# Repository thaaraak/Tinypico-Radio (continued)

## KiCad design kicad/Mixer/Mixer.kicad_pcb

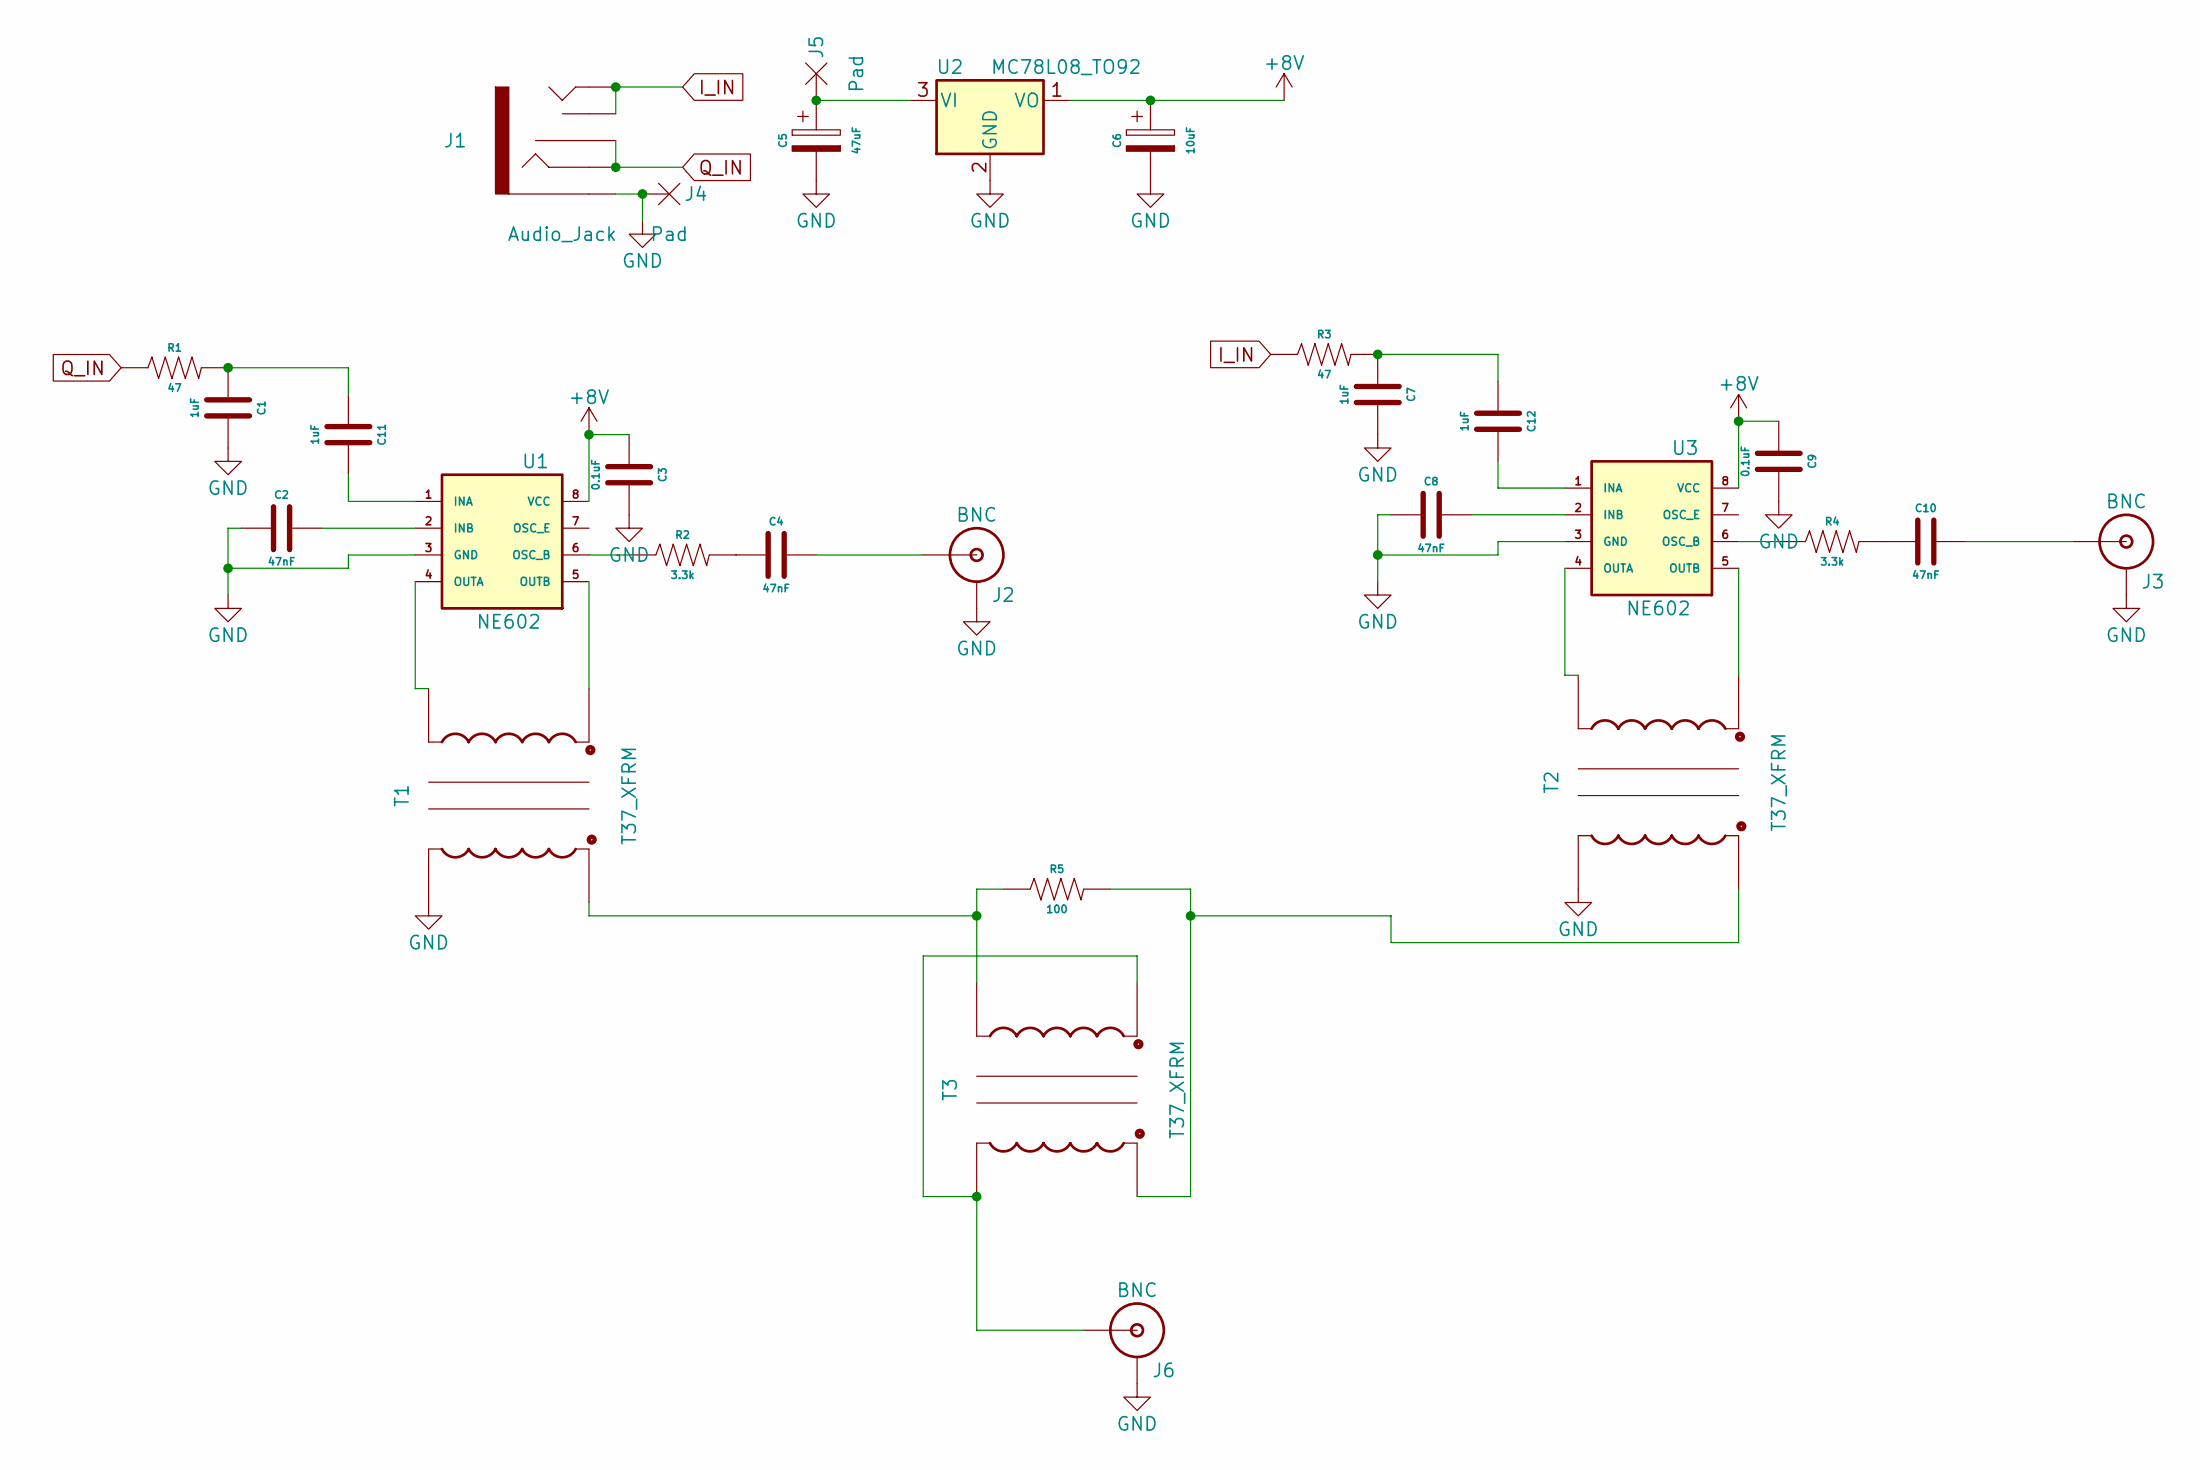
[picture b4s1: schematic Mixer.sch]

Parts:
C1, C7, C11, C12: 1uF; CAP-PTH-5MM
C2, C4, C8, C10: 47nF; CAP-PTH-5MM
C3, C9: 0.1uF; CAP-PTH-5MM
C5: 47uF; CPOL-RADIAL-2.5MM-6.5MM
C6: 10uF; CPOL-RADIAL-2.5MM-6.5MM
J1: Audio_Jack
J2, J3, J6: BNC
J4, J5: Pad
R1, R3: 47; R_Axial_DIN0204_L3.6mm_D1.6mm_P2.54mm_Vertical
R2, R4: 3.3k; R_Axial_DIN0204_L3.6mm_D1.6mm_P2.54mm_Vertical
R5: 100; R_Axial_DIN0204_L3.6mm_D1.6mm_P2.54mm_Vertical
T1, T2, T3: T37_XFRM; T37 Transformer
U1, U3: NE602; DIP8
U2: MC78L08_TO92; TO-92_Inline

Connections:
+8V: C3.1, C6.1, C9.1, U1.8 (VCC), U2.1 (VO), U3.8 (VCC)
GND: C1.2, C2.1, C3.2, C5.2, C6.2, C7.2, C8.1, C9.2, J1.SLEEVE, J2.GND, J3.GND, J4.1, J6.GND, T1.C2A, T2.C2A, U1.3 (GND), U2.2 (GND), U3.3 (GND)
I_IN: J1.TIP, J1.TSH, R3.1
unnamed: C1.1, C11.1, R1.2
unnamed: C2.2, U1.2 (INB)
unnamed: C4.1, R2.2
unnamed: C4.2, J2.S (OUT)
unnamed: C5.1, J5.1, U2.3 (VI)
unnamed: C8.2, U3.2 (INB)
unnamed: C10.1, R4.2
unnamed: C10.2, J3.S (OUT)
unnamed: C11.2, U1.1 (INA)
unnamed: C7.1, C12.1, R3.2
unnamed: C12.2, U3.1 (INA)
unnamed: J6.S (OUT), T3.C1B, T3.C2A
unnamed: R2.1, U1.6 (OSC_B)
unnamed: R4.1, U3.6 (OSC_B)
unnamed: R5.1, T1.C2B, T3.C1A
unnamed: R5.2, T2.C2B, T3.C2B
unnamed: T1.C1A, U1.4 (OUTA)
unnamed: T1.C1B, U1.5 (OUTB)
unnamed: T2.C1A, U3.4 (OUTA)
unnamed: T2.C1B, U3.5 (OUTB)
Q_IN: J1.RING, J1.RSH, R1.1

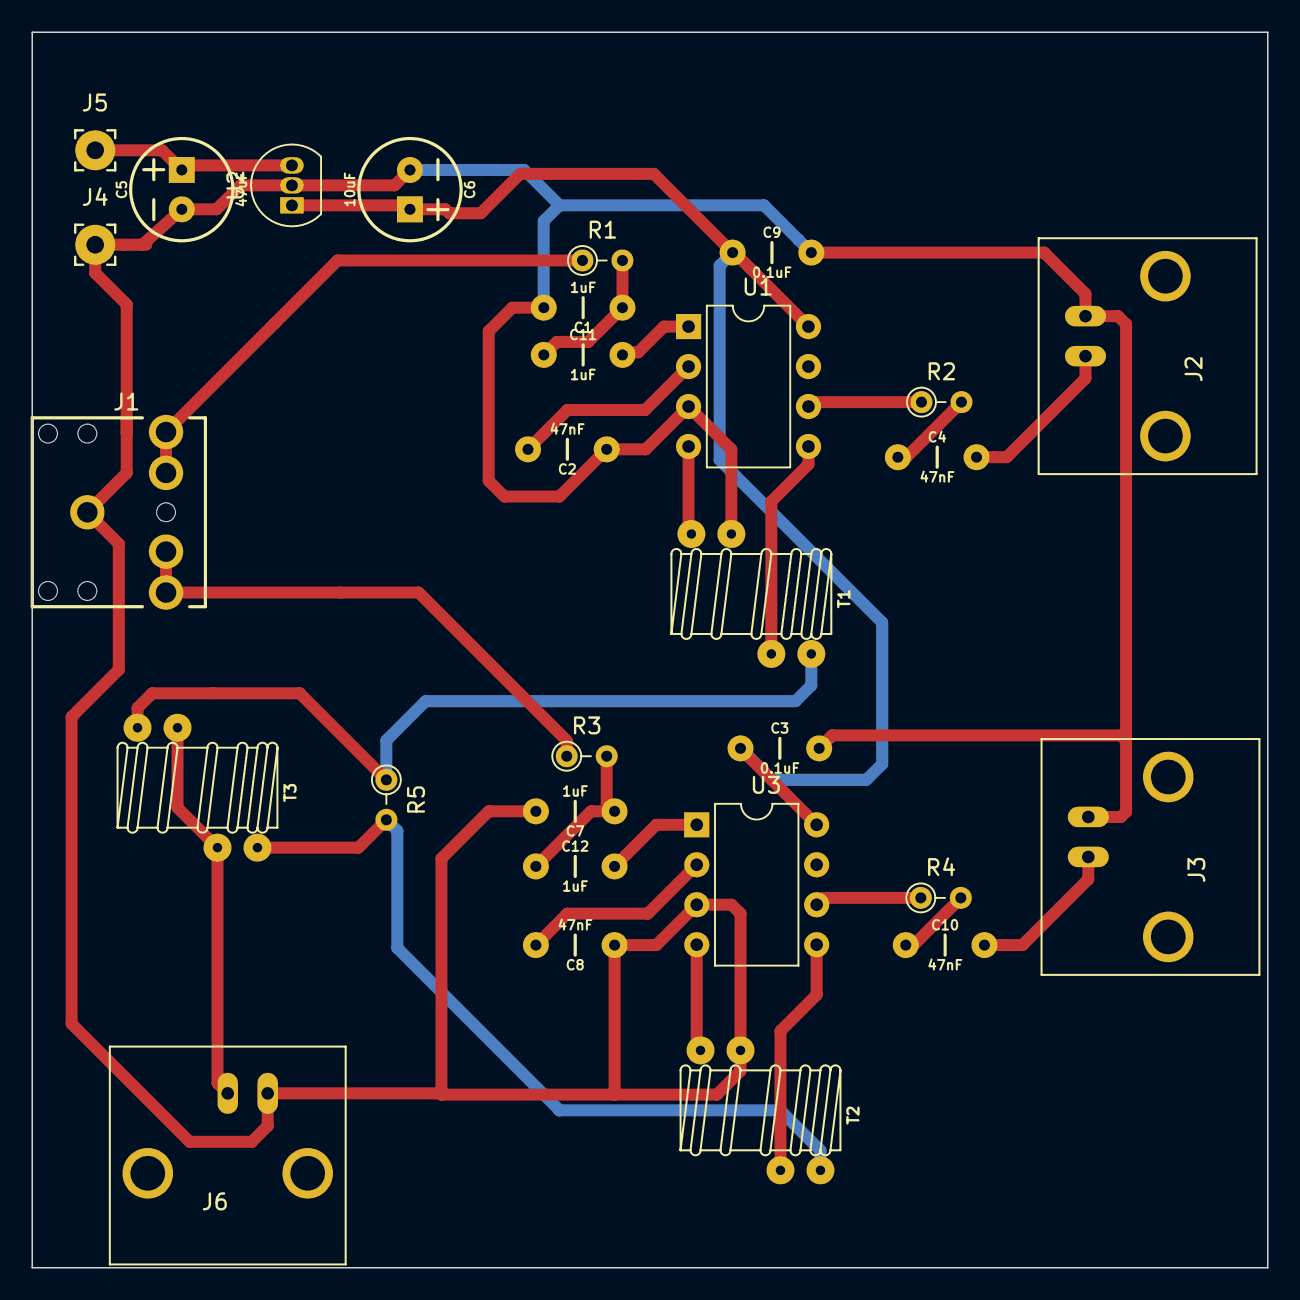
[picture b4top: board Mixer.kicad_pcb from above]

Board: 2 copper layers, 78.5 x 78.5 mm, 29 parts (0 on the bottom side), 24 nets.

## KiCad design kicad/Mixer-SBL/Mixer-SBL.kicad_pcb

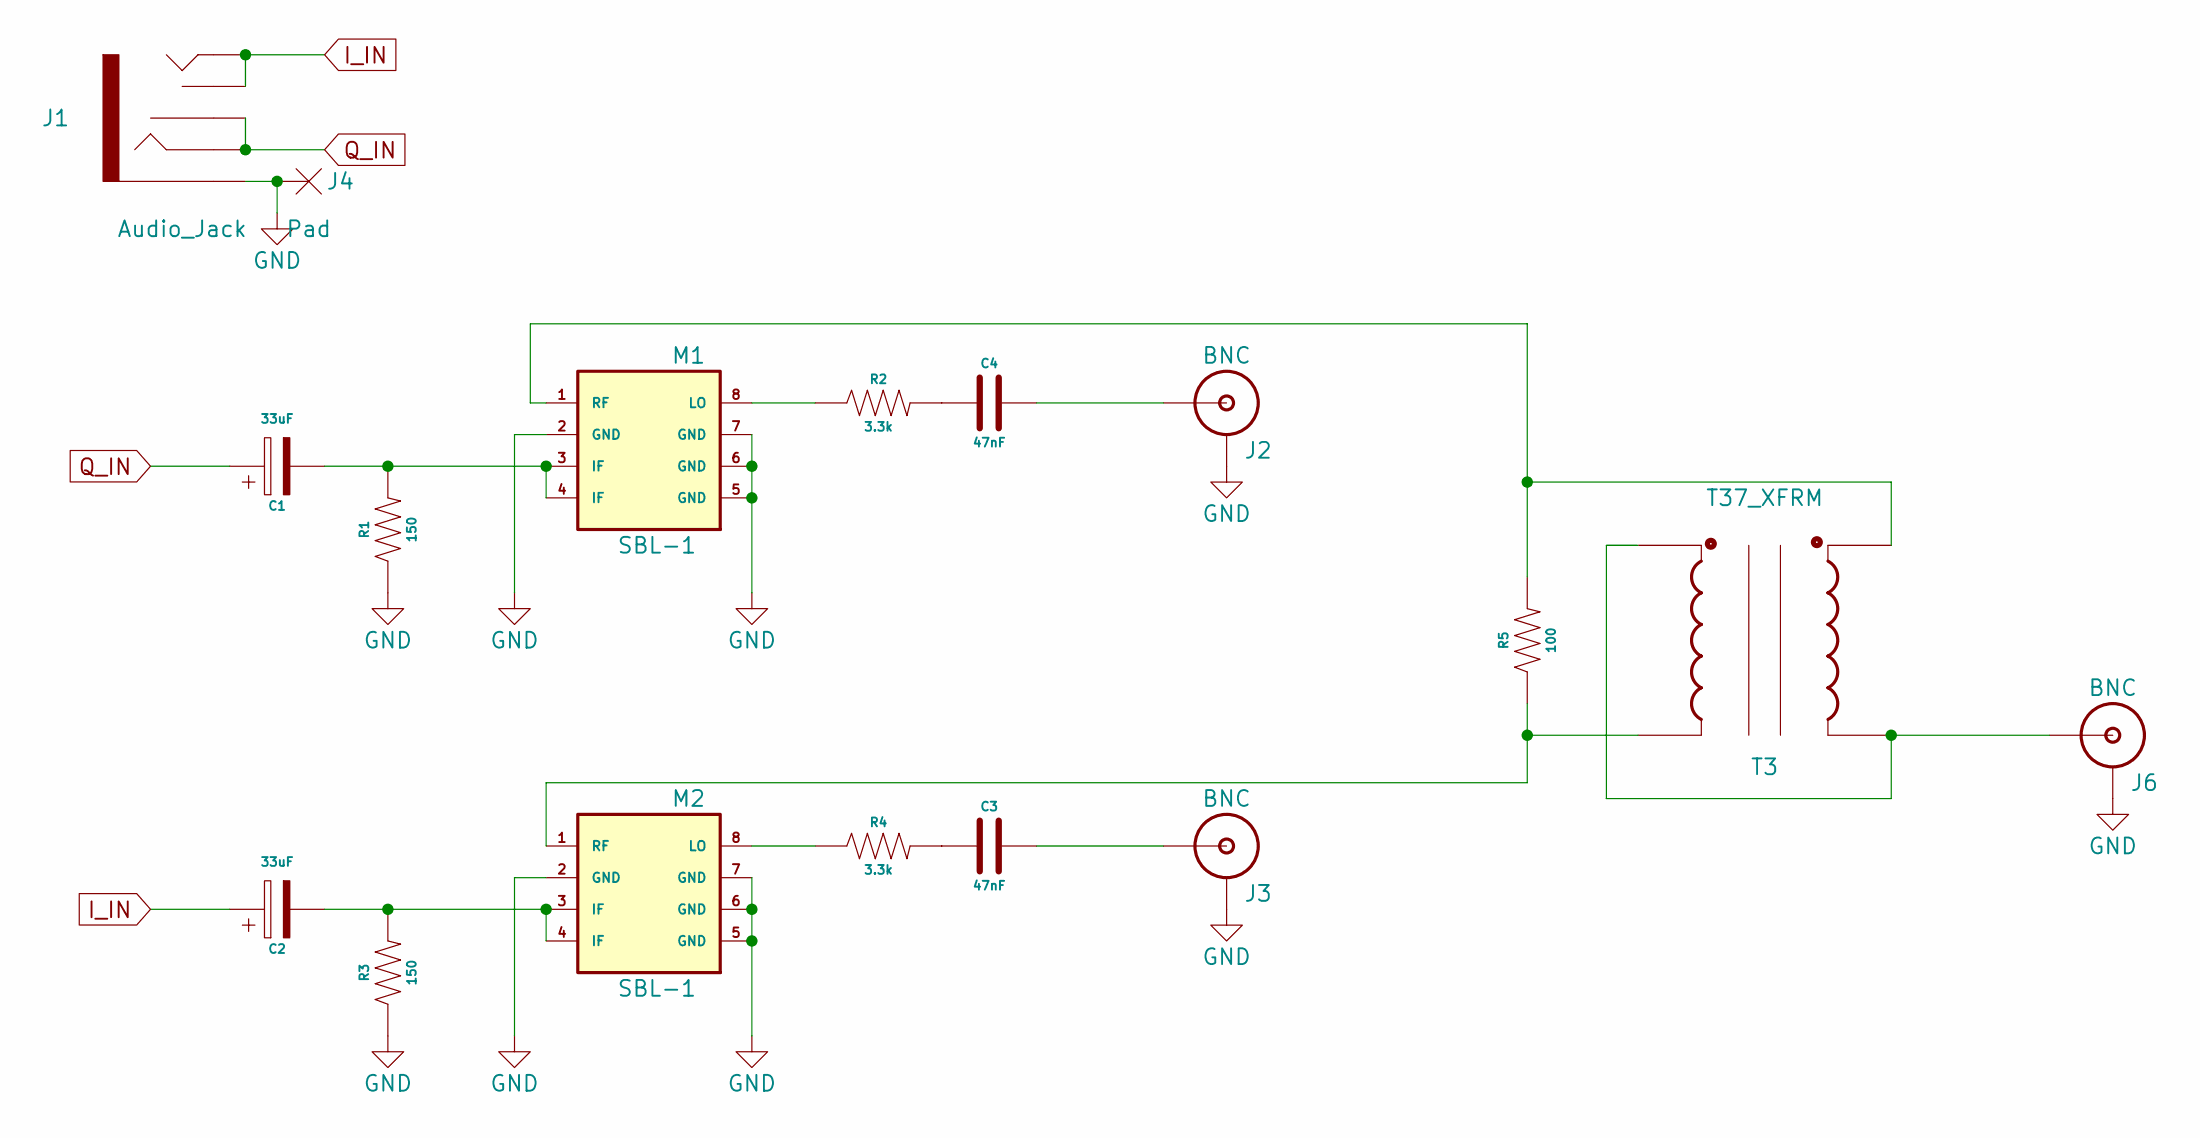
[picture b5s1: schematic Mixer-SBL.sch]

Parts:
C1, C2: 33uF; CPOL-RADIAL-2.5MM-5MM
C3, C4: 47nF; CAP-PTH-5MM
J1: Audio_Jack
J2, J3, J6: BNC
J4: Pad
M1, M2: SBL-1
R1, R3: 150; R_Axial_DIN0204_L3.6mm_D1.6mm_P2.54mm_Vertical
R2, R4: 3.3k; R_Axial_DIN0204_L3.6mm_D1.6mm_P2.54mm_Vertical
R5: 100; R_Axial_DIN0204_L3.6mm_D1.6mm_P2.54mm_Vertical
T3: T37_XFRM; T37 Transformer

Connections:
GND: J1.SLEEVE, J2.GND, J3.GND, J4.1, J6.GND, M1.2 (GND), M1.5 (GND), M1.6 (GND), M1.7 (GND), M2.2 (GND), M2.5 (GND), M2.6 (GND), M2.7 (GND), R1.1, R3.1
I_IN: C2.1, J1.TIP, J1.TSH
unnamed: C1.2, M1.3 (IF), M1.4 (IF), R1.2
unnamed: C2.2, M2.3 (IF), M2.4 (IF), R3.2
unnamed: C3.1, R4.2
unnamed: C3.2, J3.S (OUT)
unnamed: C4.1, R2.2
unnamed: C4.2, J2.S (OUT)
unnamed: J6.S (OUT), T3.C1B, T3.C2A
unnamed: M1.1 (RF), R5.2, T3.C2B
unnamed: M1.8 (LO), R2.1
unnamed: M2.1 (RF), R5.1, T3.C1A
unnamed: M2.8 (LO), R4.1
Q_IN: C1.1, J1.RING, J1.RSH

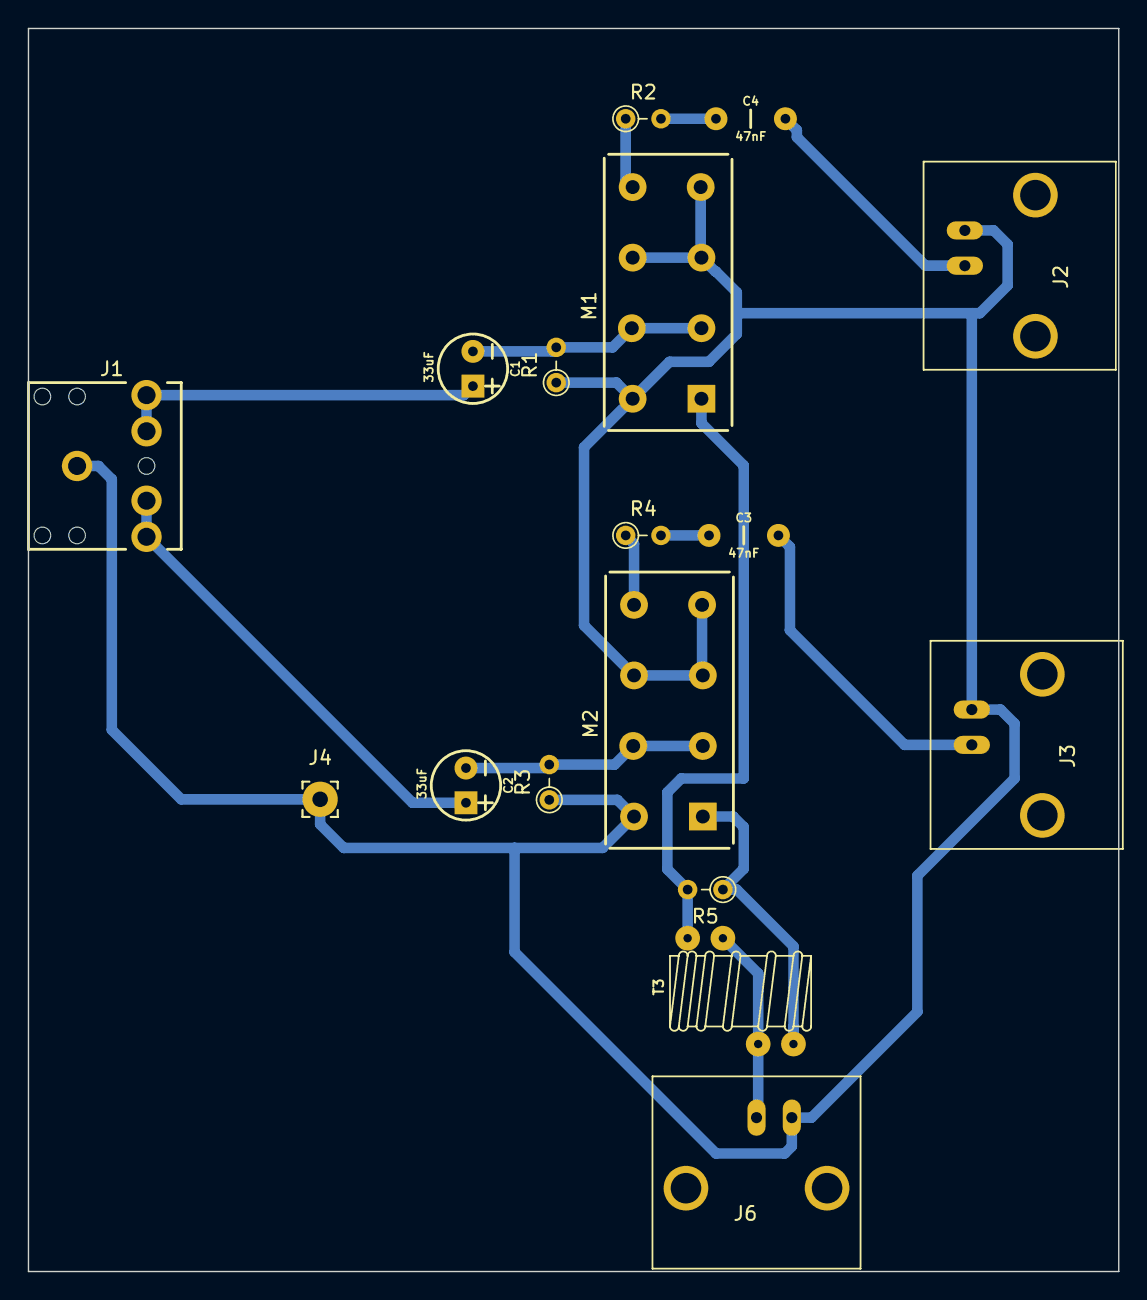
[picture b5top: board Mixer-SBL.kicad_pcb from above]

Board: 2 copper layers, 78.5 x 89.5 mm, 17 parts (0 on the bottom side), 14 nets.

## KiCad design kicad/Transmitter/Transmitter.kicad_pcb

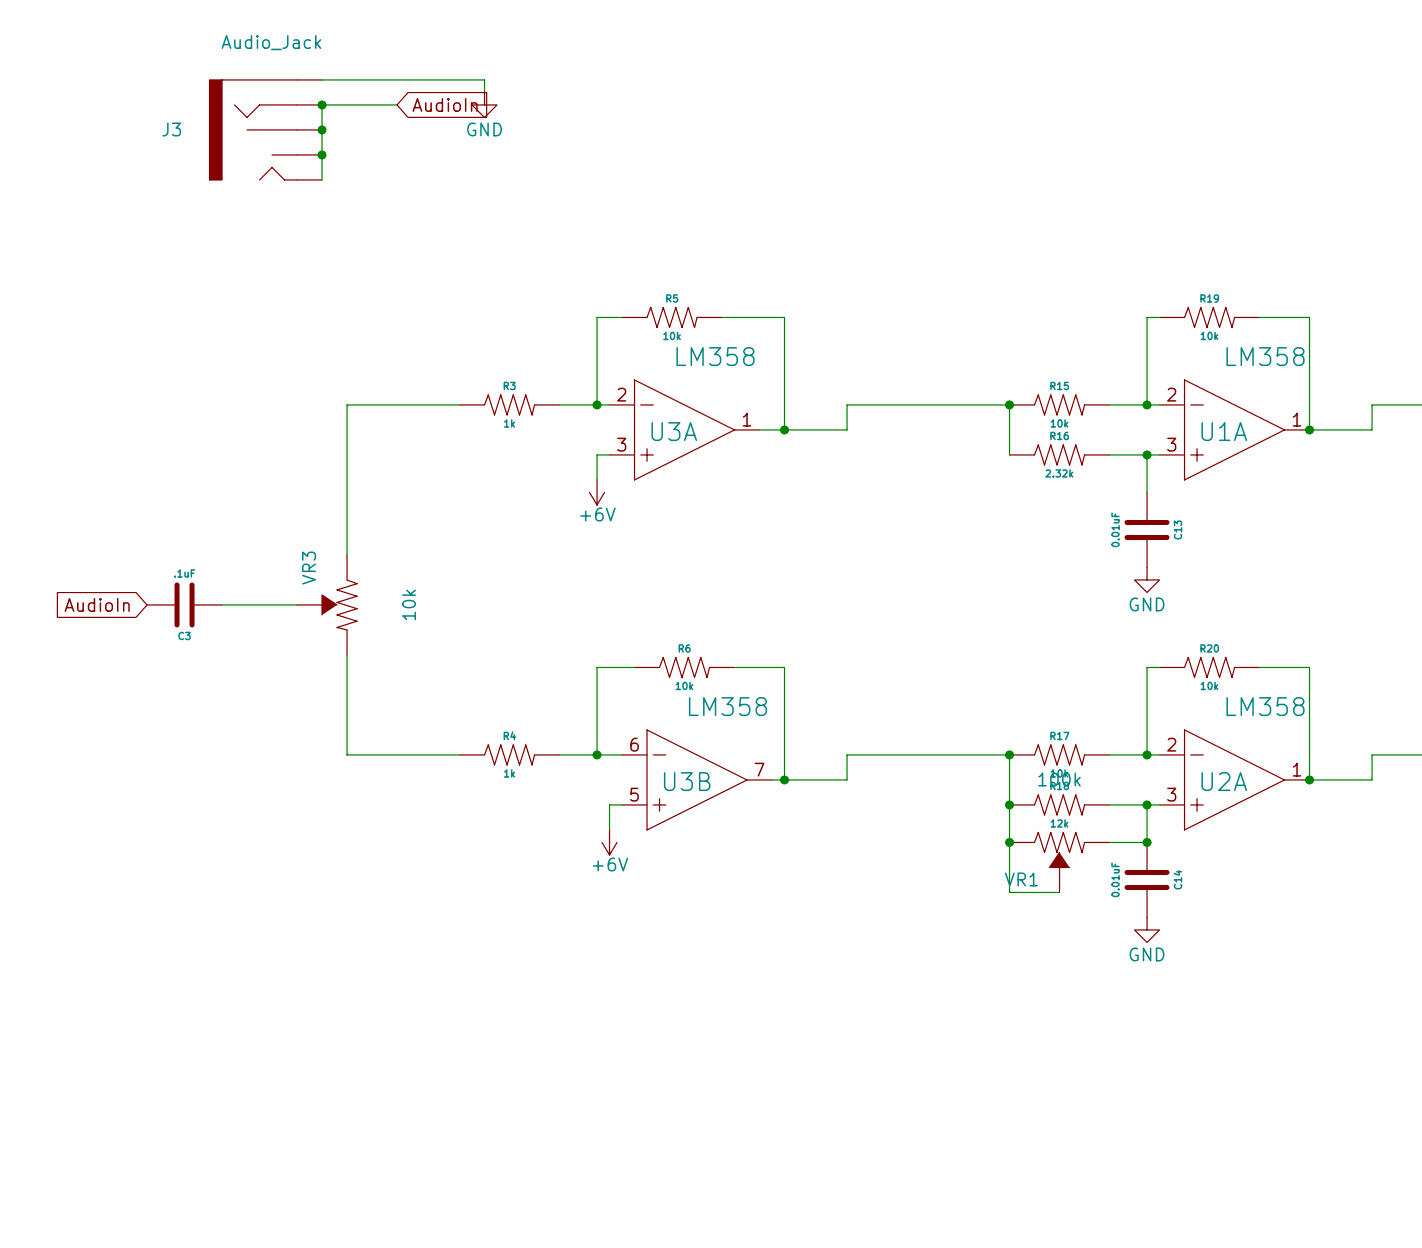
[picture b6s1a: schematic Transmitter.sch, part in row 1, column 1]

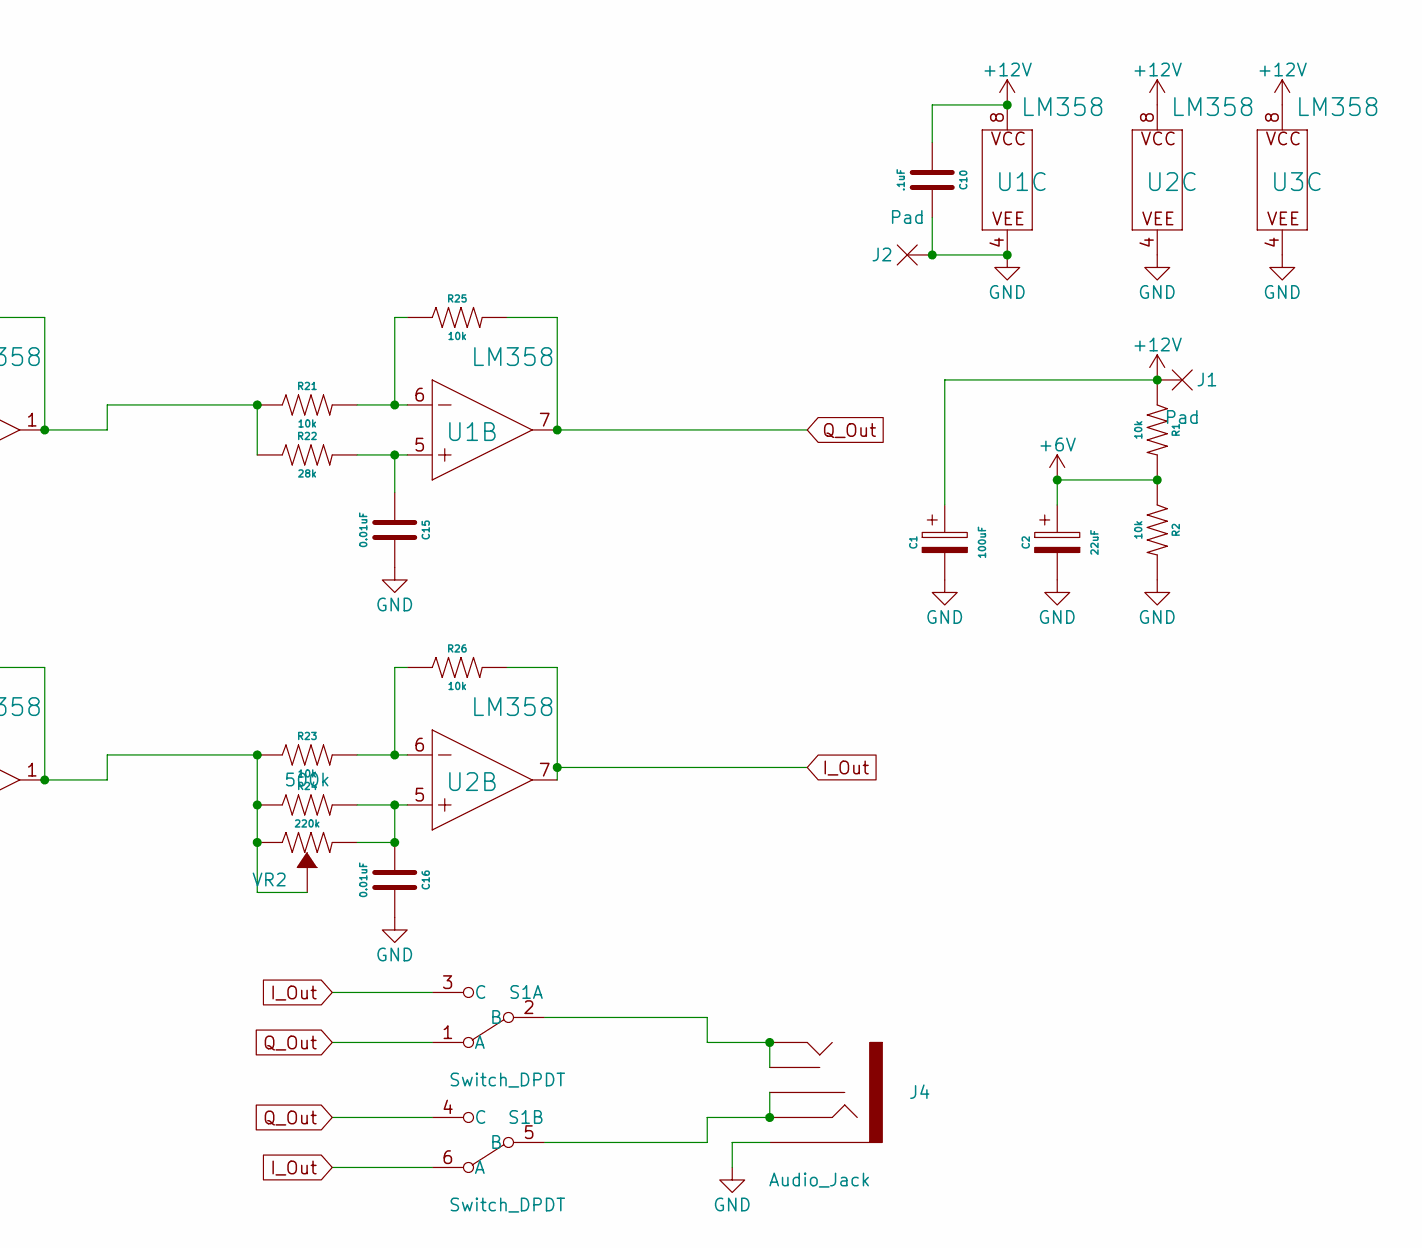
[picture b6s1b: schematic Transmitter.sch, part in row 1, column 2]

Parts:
C1: 100uF; Cap_6.3x5.4
C2: 22uF; Cap_4x5.4
C3, C10: .1uF; Capacitor 0805
C13, C14, C15, C16: 0.01uF; Capacitor 0805
J1, J2: Pad
J3, J4: Audio_Jack
R1, R2, R5, R6, R15, R17, R19, R20, R21, R23, R25, R26: 10k; Resistor 0805
R3, R4: 1k; Resistor 0805
R16: 2.32k; Resistor 0805
R18: 12k; Resistor 0805
R22: 28k; Resistor 0805
R24: 220k; Resistor 0805
S1: Switch_DPDT
U1, U2, U3: LM358; SO08
VR1: 100k; Trimpot
VR2: 500k; Trimpot
VR3: 10k; Trimpot

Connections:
+6V: C2.1, R1.2, R2.1, U3.3 (+IN), U3.5 (+IN)
+12V: C1.1, C10.1, J1.1, R1.1, U1.8 (P$V+), U2.8 (P$V+), U3.8 (P$V+)
AudioIn: C3.2, J3.RING, J3.RSH, J3.TIP, J3.TSH
GND: C1.2, C2.2, C10.2, C13.2, C14.2, C15.2, C16.2, J2.1, J3.SLEEVE, J4.SLEEVE, R2.2, U1.4 (P$V-), U2.4 (P$V-), U3.4 (P$V-)
I_Out: R26.2, S1.3 (C), S1.6 (A), U2.7 (OUT)
unnamed: C3.1, VR3.2 (WIPER)
unnamed: C13.1, R16.2, U1.3 (+IN)
unnamed: C14.1, R18.2, U2.3 (+IN), VR1.3 (CCW)
unnamed: C15.1, R22.2, U1.5 (+IN)
unnamed: C16.1, R24.2, U2.5 (+IN), VR2.3 (CCW)
unnamed: J4.RING, J4.RSH, S1.5 (B)
unnamed: J4.TIP, J4.TSH, S1.2 (B)
unnamed: R3.1, VR3.1 (CW)
unnamed: R3.2, R5.1, U3.2 (-IN)
unnamed: R4.1, VR3.3 (CCW)
unnamed: R4.2, R6.1, U3.6 (-IN)
unnamed: R5.2, R15.1, R16.1, U3.1 (OUT)
unnamed: R15.2, R19.1, U1.2 (-IN)
unnamed: R6.2, R17.1, R18.1, U3.7 (OUT), VR1.1 (CW), VR1.2 (WIPER)
unnamed: R17.2, R20.1, U2.2 (-IN)
unnamed: R19.2, R21.1, R22.1, U1.1 (OUT)
unnamed: R20.2, R23.1, R24.1, U2.1 (OUT), VR2.1 (CW), VR2.2 (WIPER)
unnamed: R21.2, R25.1, U1.6 (-IN)
unnamed: R23.2, R26.1, U2.6 (-IN)
Q_Out: R25.2, S1.1 (A), S1.4 (C), U1.7 (OUT)

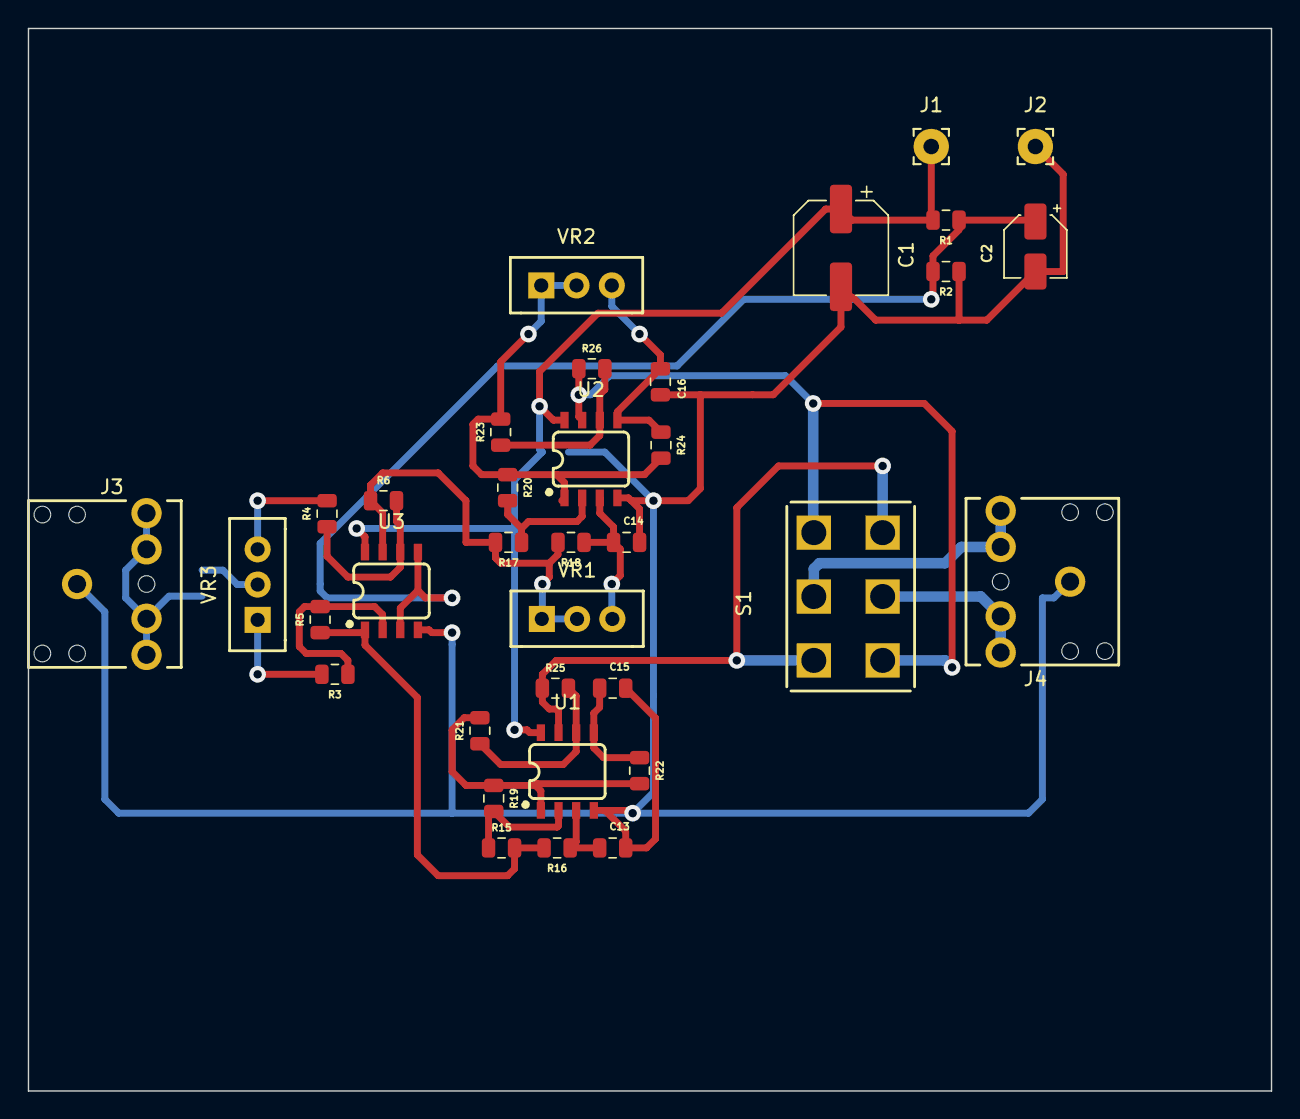
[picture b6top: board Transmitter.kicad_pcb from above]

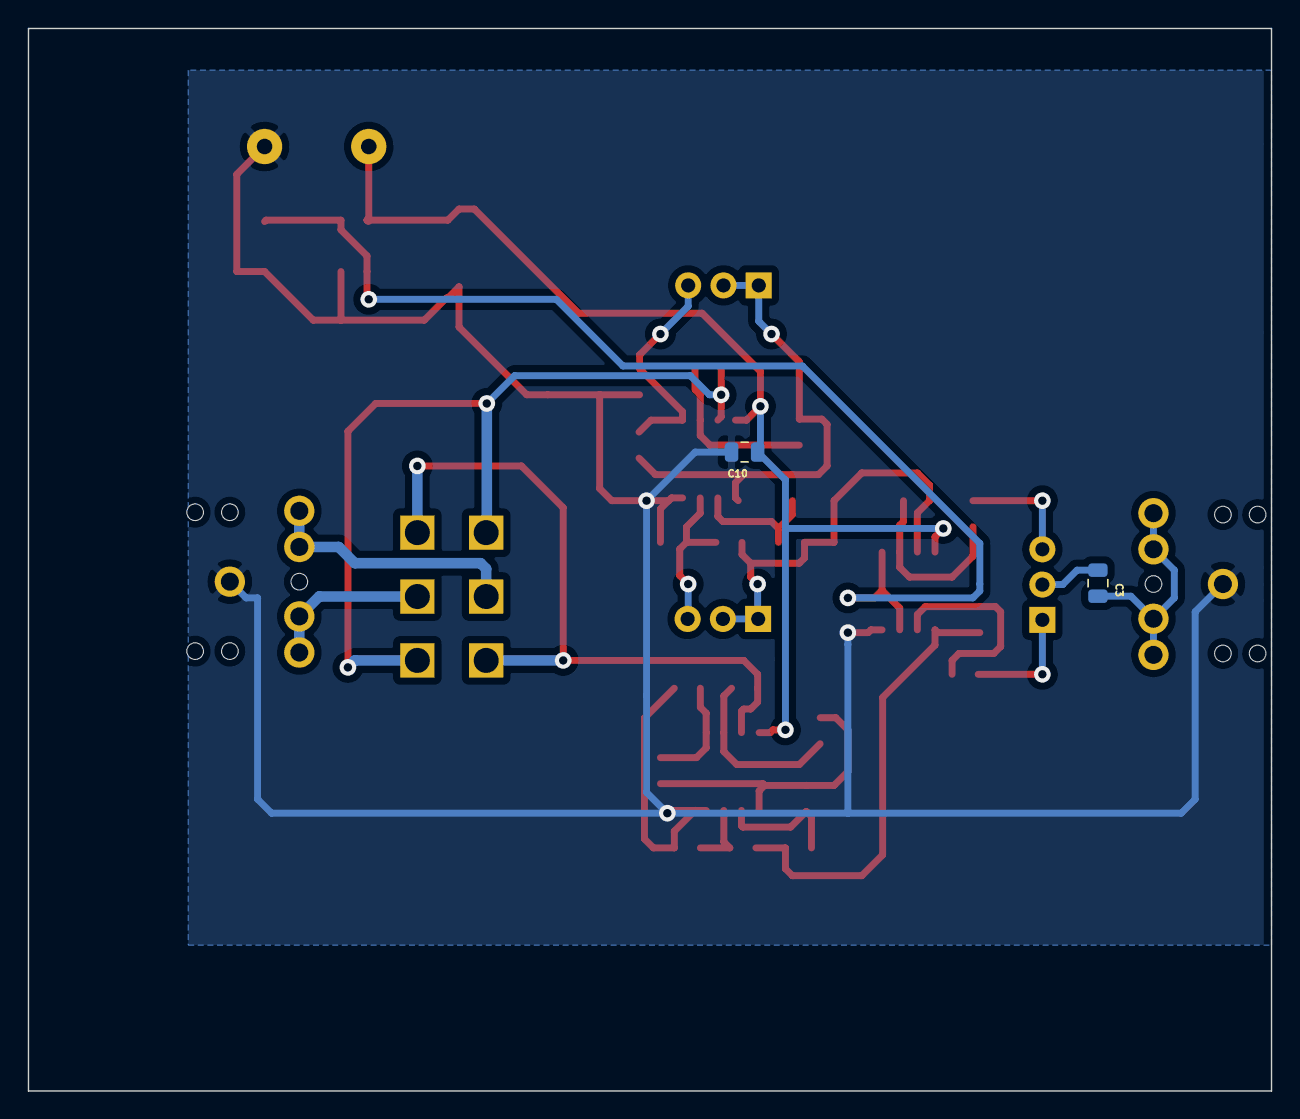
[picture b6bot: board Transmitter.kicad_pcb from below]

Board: 2 copper layers, 89.5 x 76.5 mm, 37 parts (2 on the bottom side), 25 nets.

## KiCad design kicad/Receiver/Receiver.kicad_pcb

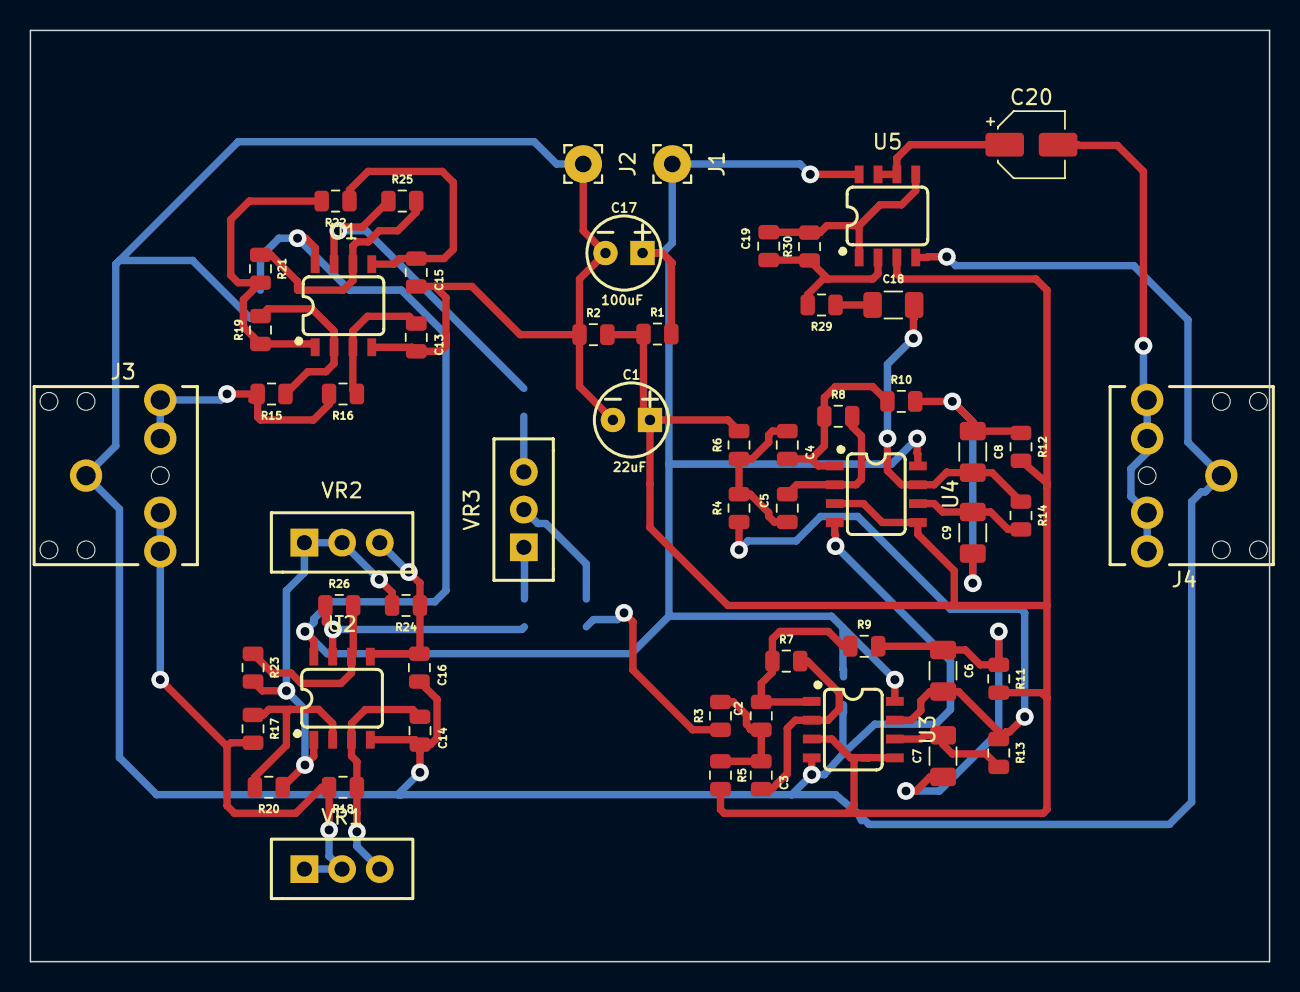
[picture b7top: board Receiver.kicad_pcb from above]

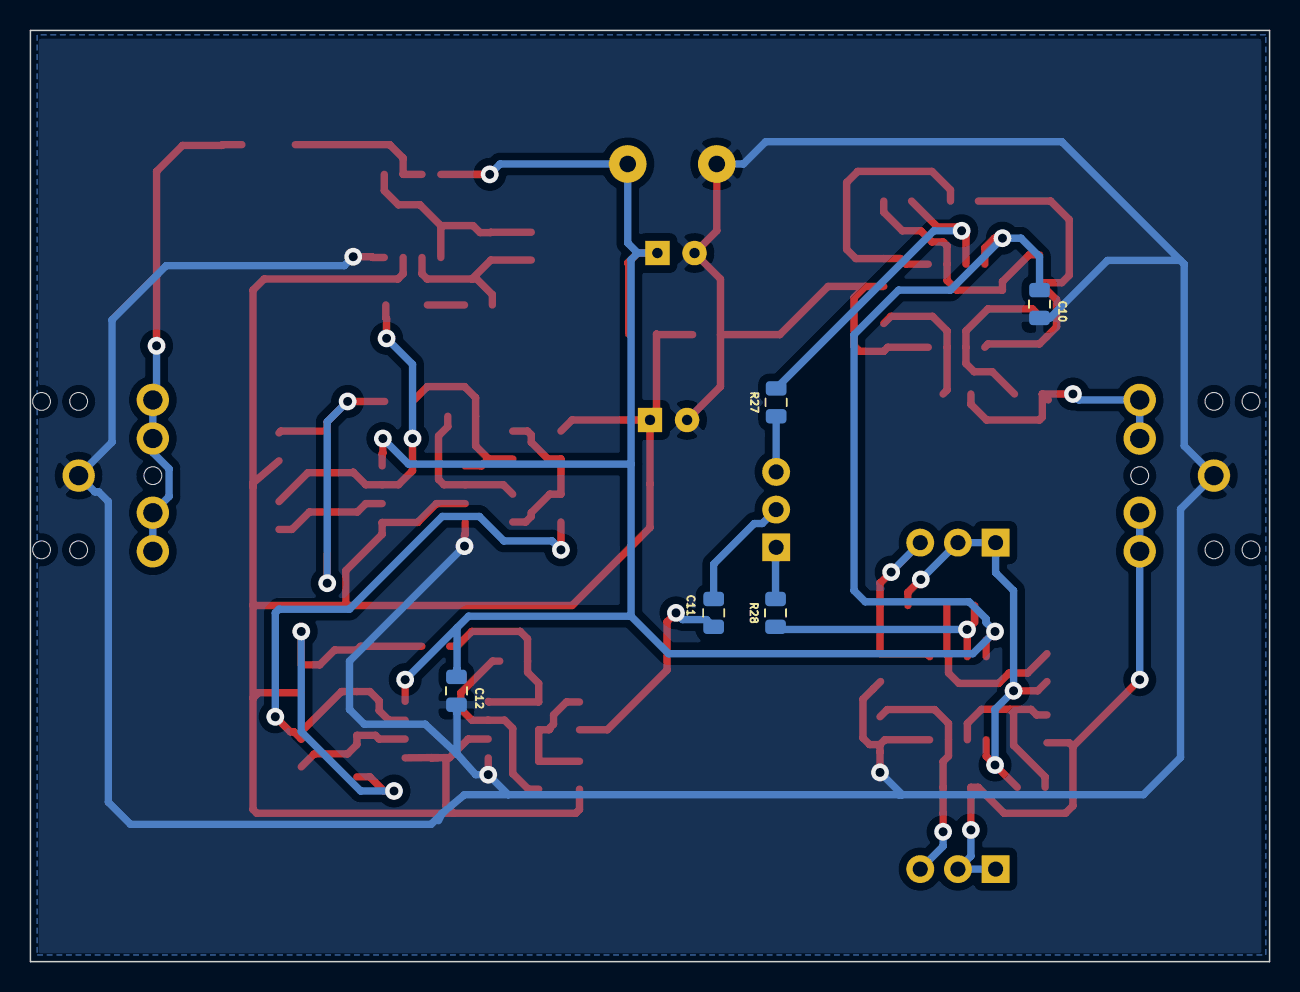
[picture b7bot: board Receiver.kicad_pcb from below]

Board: 2 copper layers, 83.5 x 62.8 mm, 62 parts (5 on the bottom side), 38 nets.

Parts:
C1: 22uF; CPOL-RADIAL-2.5MM-5MM
C2, C3, C4, C5, C19: 1nF; Capacitor 0805
C6, C7: 1.5nF; Capacitor 1206
C8, C9: 2.2nF; Capacitor 1206
C10, C11, C12: .1uF; Capacitor 0805
C13, C14, C15, C16: 0.01uF; Capacitor 0805
C17: 100uF; CPOL-RADIAL-2.5MM-5MM
C18: 1uF; Capacitor 1206
C20: 10uF; CP_Elec_4x5.4
J1, J2: Pad
J3, J4: Audio_Jack
R1, R2, R12, R15, R17, R19, R20, R21, R23, R25, R26: 10k; Resistor 0805
R3: 68k; Resistor 0805
R4: 22k; Resistor 0805
R5: 33k; Resistor 0805
R6: 4.7k; Resistor 0805
R7: 220k; Resistor 0805
R8: 470k; Resistor 0805
R9: 100k; Resistor 0805
R10, R11: 47k; Resistor 0805
R13: 330k; Resistor 0805
R14: 1M; Resistor 0805
R16: 2.32k; Resistor 0805
R18: 12k; Resistor 0805
R22: 28k; Resistor 0805
R24, R30: 120k; Resistor 0805
R27, R28, R29: 1k; Resistor 0805
U1, U2, U3, U4, U5: LM358; SO08
VR1, VR2, VR3: Trimpot

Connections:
+6V: C1.1, R1.2, R2.1, R5.1, R6.1, R11.1, R12.1, U3.3, U3.5, U4.3, U4.5, U5.3
+12V: C10.1, C12.1, C17.1, J1.1, R1.1, U1.8, U2.8, U3.8, U4.8, U5.8
FilterOut: C8.2, C18.2, R14.2, U4.7
GND: C1.2, C10.2, C12.2, C13.2, C14.2, C15.2, C16.2, C17.2, J2.1, J3.SLEEVE, J4.SLEEVE, R2.2, U1.4, U2.4, U3.4, U4.4, U5.4
I_In: J3.TIP, J3.TSH, R17.1, R18.1, VR1.1, VR1.2
unnamed: C2.1, C3.1, R3.1, R5.2
unnamed: C2.2, R7.2, R9.2, U3.1
unnamed: C3.2, R7.1, U3.2
unnamed: C4.1, C5.1, R4.1, R6.2
unnamed: C4.2, R8.2, R10.2, U4.1
unnamed: C5.2, R8.1, U4.2
unnamed: C6.1, C7.1, R9.1, R11.2
unnamed: C6.2, R4.2, R13.2, U3.7
unnamed: C7.2, R13.1, U3.6
unnamed: C8.1, C9.1, R10.1, R12.2
unnamed: C9.2, R14.1, U4.6
unnamed: C11.1, R3.2
unnamed: C13.1, R16.2, U1.3
unnamed: C14.1, R18.2, U2.3, VR1.3
unnamed: C15.1, R22.2, U1.5
unnamed: C16.1, R24.2, U2.5, VR2.3
unnamed: C18.1, R29.2
unnamed: C19.1, R29.1, R30.2, U5.2
unnamed: C19.2, R30.1, U5.1, U5.5
unnamed: C20.1, U5.6, U5.7
unnamed: C20.2, J4.RING, J4.RSH, J4.TIP, J4.TSH
unnamed: R15.2, R19.1, U1.2
unnamed: R17.2, R20.1, U2.2
unnamed: R19.2, R21.1, R22.1, U1.1
unnamed: R20.2, R23.1, R24.1, U2.1, VR2.1, VR2.2
unnamed: R21.2, R25.1, U1.6
unnamed: R23.2, R26.1, U2.6
unnamed: R25.2, R27.1, U1.7
unnamed: R26.2, R28.2, U2.7
unnamed: R27.2, VR3.3
unnamed: R28.1, VR3.1
Phase_Out: C11.2, VR3.2
Q_In: J3.RING, J3.RSH, R15.1, R16.1
